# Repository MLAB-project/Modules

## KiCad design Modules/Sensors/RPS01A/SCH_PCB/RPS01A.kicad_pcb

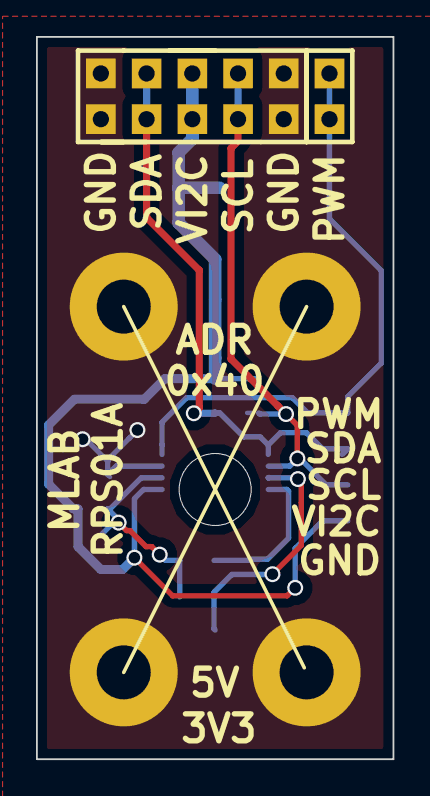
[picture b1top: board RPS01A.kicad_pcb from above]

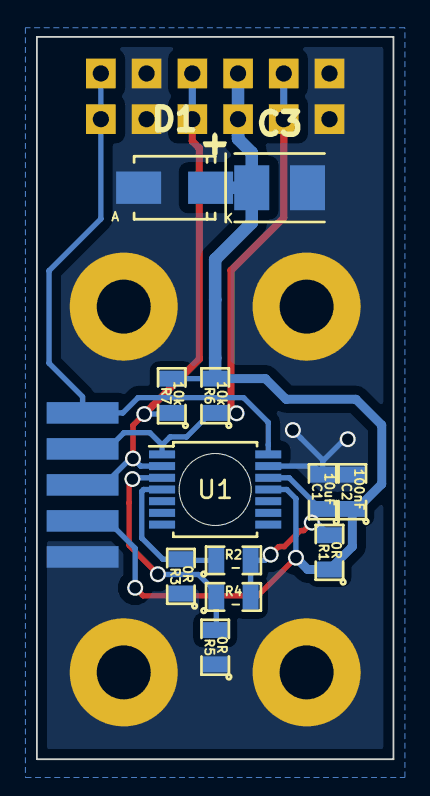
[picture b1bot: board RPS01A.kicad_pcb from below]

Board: 2 copper layers, 19.8 x 40.1 mm, 19 parts (13 on the bottom side), 8 nets.

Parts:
C1: 10uF; SMD-0805
C2: 100nF; SMD-0805
C3: 10uF; TantalC_SizeB_Reflow
D1: M4; SMA_Standard
J1: JUMP_5X2; Pin_Header_Straight_2x05
J2: JUMP_2x1; Pin_Header_Straight_2x01
J3: JUMP_5X2; SMD_JUMP1X5
P1, P2, P3, P4: _; MountingHole_3mm
R1, R3, R5: 0R; SMD-0805
R2, R4: -; SMD-0805
R6, R7: 10k; SMD-0805
U1: AS5048B; TSSOP-14_4.4x5mm_Pitch0.65mm

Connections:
/A1: R2.1, R3.2, U1.4
/A2: R4.1, R5.2, U1.3
/PWM: J2.1, J2.2, J3.5, U1.14
/SCL: J1.2, J1.9, J3.3, R7.1, U1.2
/SDA: J1.4, J1.7, J3.4, R6.1, U1.1
/VDD3V: C1.1, R1.2, R2.2, R4.2, U1.12
GND: C1.2, C2.2, C3.2, D1.1, J1.1, J1.5, J1.6, J1.10, J3.1, P1.1, P2.1, P3.1, P4.1, R3.1, R5.1, U1.13
VDD: C2.1, C3.1, D1.2, J1.3, J1.8, J3.2, R1.1, R6.2, R7.2, U1.11

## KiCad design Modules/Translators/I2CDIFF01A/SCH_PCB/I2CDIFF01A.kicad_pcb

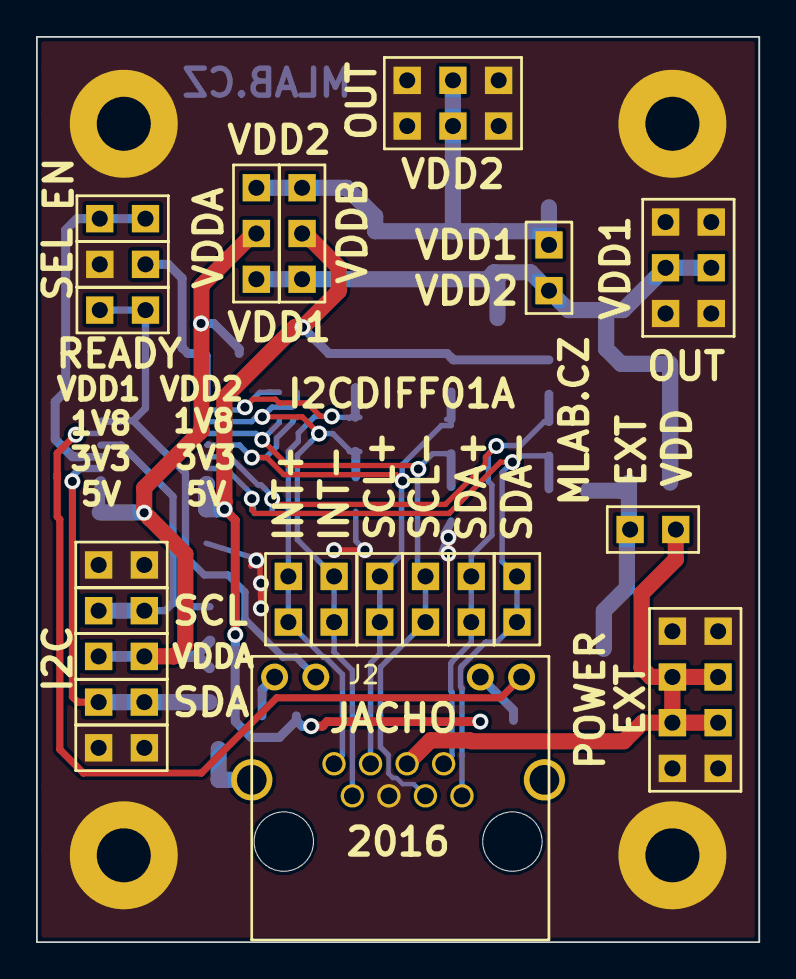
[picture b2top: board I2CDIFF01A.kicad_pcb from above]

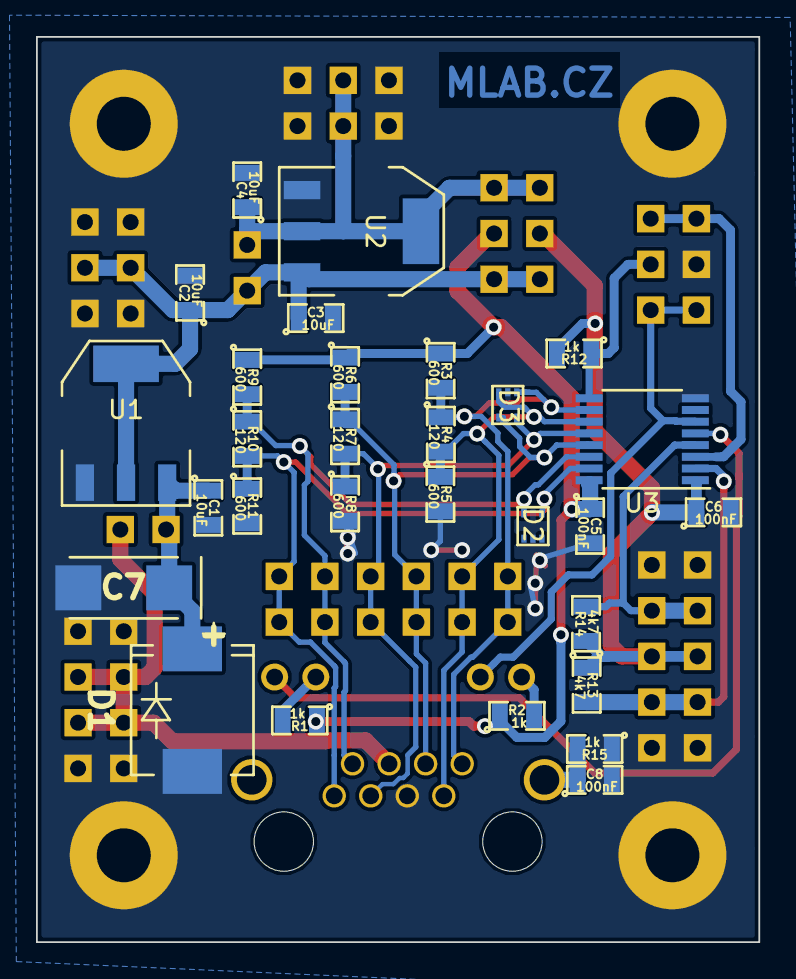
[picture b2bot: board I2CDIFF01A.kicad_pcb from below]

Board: 2 copper layers, 40.1 x 50.3 mm, 55 parts (29 on the bottom side), 22 nets.

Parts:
C1, C2, C3, C4: 10uF; SMD-0805
C5, C6, C8: 100nF; SMD-0805
C7: 47uF; TantalC_SizeC_Reflow
D1: SM15T18A; Diode-SMC_Standard
D2, D3: SP1001-04XTG; SOT-553
J1: JUMP_4X2; Straight_2x04
J2: RJ45_RJHSE-5384; RJHSE-5384(RJ45)
J3, J19, J20, J21, J22, J23: JUMP_2x1; Straight_1x02
J4, J5, J6, J7, J8, J9: JUMP_2x1; Straight_2x01
J10, J13: JUMP_3X2; Straight_2x03
J11, J14, J17: JUMP2_2x1; Straight_2x01
J12, J15: CONN_3; Straight_1x03
J16: EN; Straight_1x02
M1, M2, M3, M4: HOLE; MountingHole_3mm
R1, R2, R12, R15: 1k; SMD-0805
R3, R5, R6, R8, R9, R11: 600; SMD-0805
R4, R7, R10: 120; SMD-0805
R13, R14: 4k7; SMD-0805
U1: LM1117 5V; SOT-223
U2: LM1117 3V3; SOT-223
U3: PCA9616; TSSOP-16_4.4x5mm_Pitch0.65mm

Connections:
/EN: J16.1, J16.2, U3.3
/INT+: D3.1, J2.8, J4.1, J4.2, R3.2, R4.1, U3.10
/INT-: D3.3, J2.7, J5.1, J5.2, R4.2, R5.1, U3.11
/PIDENT: J2.9, U3.5
/READY: J2.11, J3.1, J3.2, U3.6
/SCL+: D3.4, J2.6, J6.1, J6.2, R6.2, R7.1, U3.13
/SCL-: D3.5, J2.3, J7.1, J7.2, R7.2, R8.1, U3.12
/SDA+: D2.5, J2.2, J8.1, J8.2, R9.2, R10.1, U3.14
/SDA-: D2.4, J2.1, J9.1, J9.2, R10.2, R11.1, U3.15
/VDD1: C2.1, C3.1, J10.3, J10.4, J11.2, J12.3, J15.3, U1.2, U1.4, U2.3
/VDD2: C4.1, J11.1, J12.1, J13.3, J13.4, J15.1, U2.2, U2.4
/VddA: C6.1, J15.2, J21.1, J21.2, R12.2, R13.1, R14.1, U3.1
/VddB: C5.1, J12.2, R1.1, R2.1, R3.1, R6.1, R9.1, U3.16
GND: C1.2, C2.2, C3.2, C4.2, C5.2, C6.2, C7.2, C8.2, D1.1, D2.2, D3.2, J1.1, J1.2, J1.7, J1.8, J2.5, J10.1, J10.2, J10.5, J10.6, J13.1, J13.2, J13.5, J13.6, J14.1, J19.1, J19.2, J23.1, J23.2, M1.1, M2.1, M3.1, M4.1, R5.2, R8.2, R11.2, R15.1, U1.1, U2.1, U3.8
unnamed: C8.1, J2.13, R15.2
unnamed: J2.10, R1.2
unnamed: J2.12, R2.2
unnamed: J14.2, R12.1, U3.9
SCL: J22.1, J22.2, R14.2, U3.4
SDA: J20.1, J20.2, R13.2, U3.2
VCC: J1.3, J1.4, J1.5, J1.6, J2.4, J17.2
VDD: C1.1, C7.1, D1.2, J17.1, U1.3

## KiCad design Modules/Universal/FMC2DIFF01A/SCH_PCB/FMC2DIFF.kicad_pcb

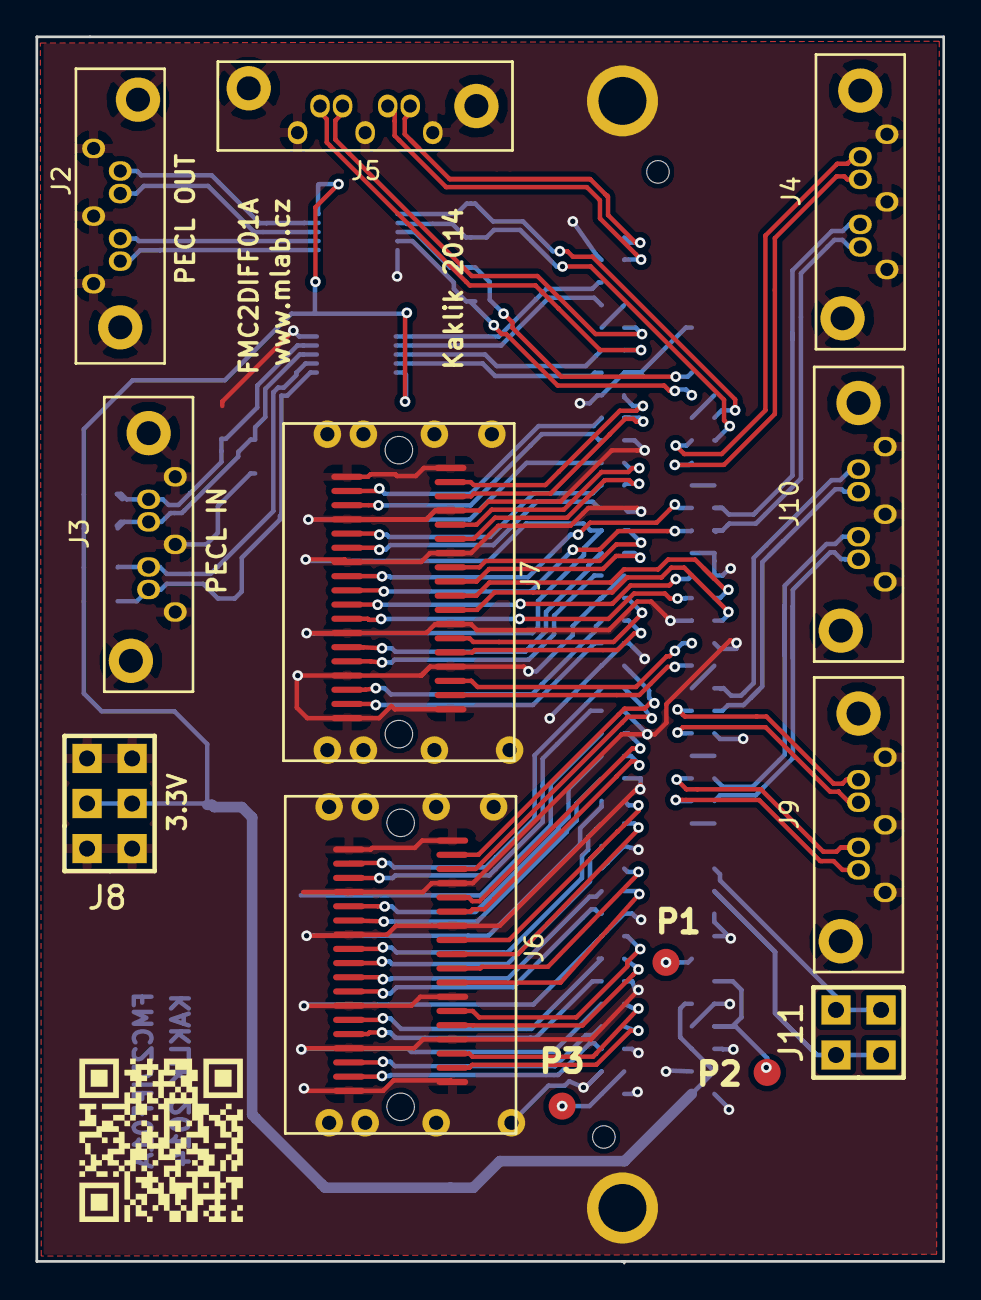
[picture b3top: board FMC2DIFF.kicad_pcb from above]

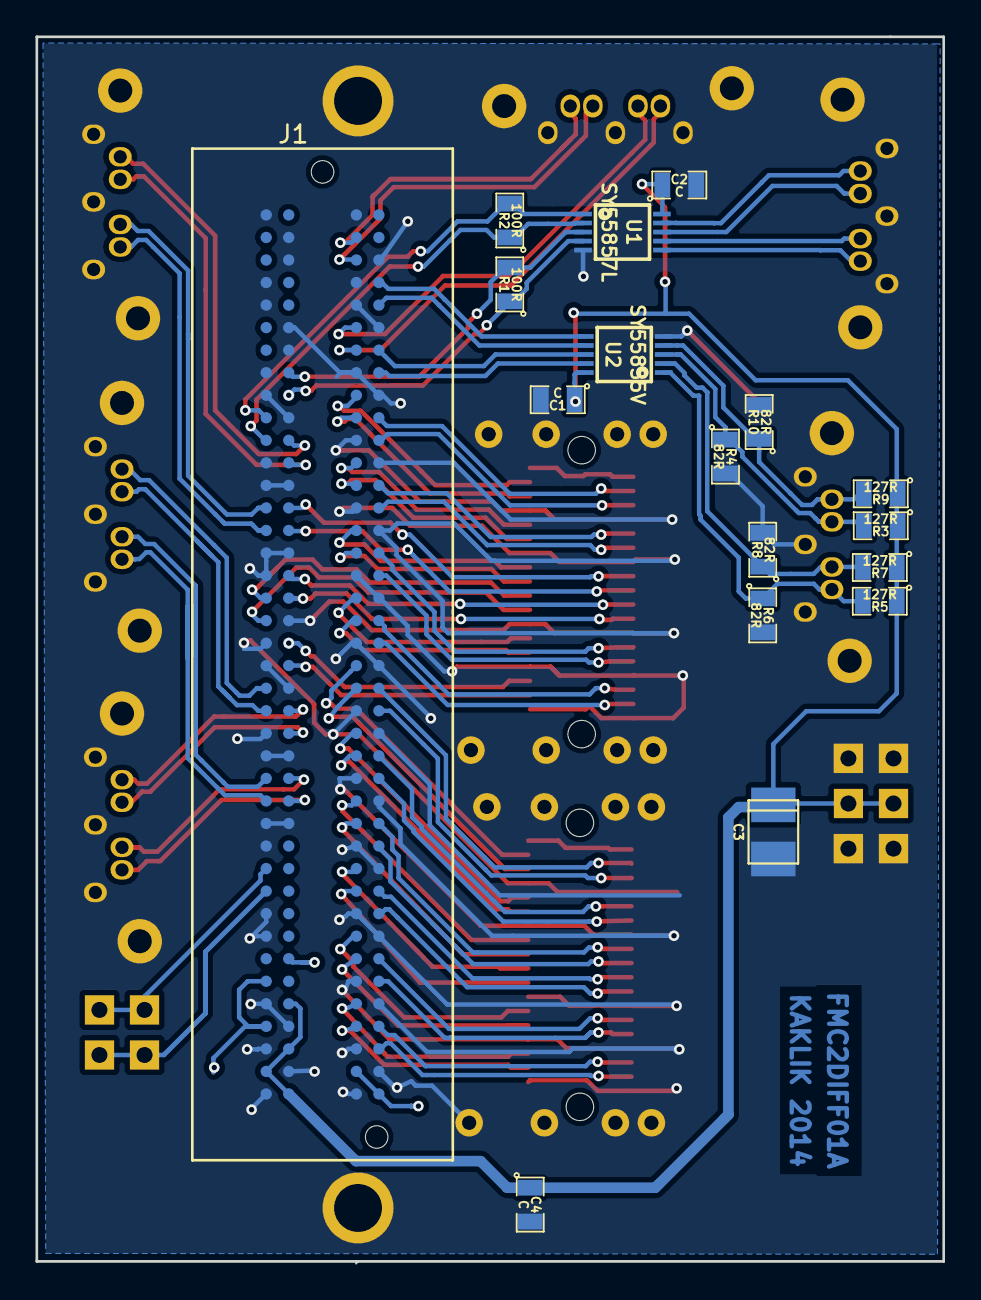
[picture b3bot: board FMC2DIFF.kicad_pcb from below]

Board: 2 copper layers, 51.1 x 69.1 mm, 30 parts (17 on the bottom side), 87 nets.

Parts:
C1, C2, C4: C; SM0805
C3: CP1; c_tant_B
J1: ASP-134604-01_(FMC); FMC_LPC_ASP-134604-01
J2, J3, J4, J5, J9, J10: SATA7-67491-1030; SATA-7_THT_VERT
J6, J7: SAS_mini_1888174
J8: JUMP_3X2_CONN; Pin_Header_Straight_2x03
J11: JUMP_2X2_CONN; Pin_Header_Straight_2x02
P1, P2, P3: CONN_1; Measurement_Point_Round-SMD-Pad_Small
R1, R2: 100R; SM0805
R3, R5, R7, R9: 127R; SM0805
R4, R6, R8, R10: 82R; SM0805
U1: SY55857L; MSOP10-0.5
U2: SY55855V; MSOP10-0.5

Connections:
3V3: C1.1, C2.1, C3.1, C4.1, J1.C39, J1.D36, J1.D38, J1.D40, J8.2, J8.5, R3.1, R5.1, R7.1, R9.1, U1.10, U2.10
+12V: J1.C35, J1.C37, P2.1
CLK0_M2C_N: J1.H05, U2.7
CLK0_M2C_P: J1.H04, U2.6
CLK1_M2C_N: J1.G03, J5.3
CLK1_M2C_P: J1.G02, J5.2
DGND: C1.2, C2.2, C3.2, C4.2, J1.C01, J1.C04, J1.C05, J1.C08, J1.C09, J1.C12, J1.C13, J1.C16, J1.C17, J1.C20, J1.C21, J1.C24, J1.C25, J1.C28, J1.C29, J1.C32, J1.C33, J1.C36, J1.C38, J1.C40, J1.D02, J1.D03, J1.D06, J1.D07, J1.D10, J1.D13, J1.D16, J1.D19, J1.D22, J1.D25, J1.D28, J1.D37, J1.D39, J1.G01, J1.G04, J1.G05, J1.G08, J1.G11, J1.G14, J1.G17, J1.G20, J1.G23, J1.G26, J1.G29, J1.G32, J1.G35, J1.G38, J1.G40, J1.H03, J1.H06, J1.H09, J1.H12, J1.H15, J1.H18, J1.H21, J1.H24, J1.H27, J1.H30, J1.H33, J1.H36, J1.H39, J2.1, J2.4, J2.7, J2.8, J2.9, J3.1, J3.4, J3.7, J3.8, J3.9, J4.1, J4.4, J4.7, J4.8, J4.9, J5.1, J5.4, J5.7, J5.8, J5.9, J6.1, J6.2, J6.3, J6.4, J6.5, J6.6, J6.7, J6.8, J6.A1, J6.A4, J6.A7, J6.A12, J6.A15, J6.A18, J6.B1, J6.B4, J6.B7, J6.B12, J6.B15, J6.B18, J7.1, J7.2, J7.3, J7.4, J7.5, J7.6, J7.7, J7.8, J7.A1, J7.A4, J7.A7, J7.A12, J7.A15, J7.A18, J7.B1, J7.B4, J7.B7, J7.B12, J7.B15, J7.B18, J8.1, J8.3, J8.4, J8.6, J9.1, J9.4, J9.7, J9.8, J9.9, J10.1, J10.4, J10.7, J10.8, J10.9, R4.2, R6.2, R8.2, R10.2, U1.5, U2.5
LA00_N_CC: J1.G07, J5.6
LA00_P_CC: J1.G06, J5.5
LA01_N_CC: J1.D09, R1.1, U1.4
LA01_P_CC: J1.D08, R1.2, U1.3
LA02_N: J1.H08, U2.9
LA02_P: J1.H07, U2.8
LA03_N: J1.G10, J7.B3
LA03_P: J1.G09, J7.B2
LA04_N: J1.H11, J7.A3
LA04_P: J1.H10, J7.A2
LA05_N: J1.D12, J4.3
LA05_P: J1.D11, J4.2
LA06_N: J1.C11, R2.1, U1.2
LA06_P: J1.C10, R2.2, U1.1
LA07_N: J1.H14, J7.A6
LA07_P: J1.H13, J7.A5
LA08_N: J1.G13, J7.B6
LA08_P: J1.G12, J7.B5
LA09_N: J1.D15, J7.A9
LA09_P: J1.D14, J7.A8
LA10_N: J1.C15, J4.6
LA10_P: J1.C14, J4.5
LA11_N: J1.H17, J7.A14
LA11_P: J1.H16, J7.A13
LA12_N: J1.G16, J7.B9
LA12_P: J1.G15, J7.B8
LA13_N: J1.D18, J7.A11
LA13_P: J1.D17, J7.A10
LA14_N: J1.C19, J7.B11
LA14_P: J1.C18, J7.B10
LA15_N: J1.H20, J7.A17
LA15_P: J1.H19, J7.A16
LA16_N: J1.G19, J7.B14
LA16_P: J1.G18, J7.B13
LA17_N_CC: J1.D21, J7.B17
LA17_P_CC: J1.D20, J7.B16
LA18_N_CC: J1.C23, J10.3
LA18_P_CC: J1.C22, J10.2
LA19_N: J1.H23, J6.A3
LA19_P: J1.H22, J6.A2
LA20_N: J1.G22, J6.B3
LA20_P: J1.G21, J6.B2
LA21_N: J1.H26, J6.A6
LA21_P: J1.H25, J6.A5
LA22_N: J1.G25, J6.B6
LA22_P: J1.G24, J6.B5
LA23_N: J1.D24, J9.3
LA23_P: J1.D23, J9.2
LA24_N: J1.H29, J6.A9
LA24_P: J1.H28, J6.A8
LA25_N: J1.G28, J6.B9
LA25_P: J1.G27, J6.B8
LA26_N: J1.D27, J9.6
LA26_P: J1.D26, J9.5
LA27_N: J1.C27, J10.6
LA27_P: J1.C26, J10.5
LA28_N: J1.H32, J6.A11
LA28_P: J1.H31, J6.A10
LA29_N: J1.G31, J6.B11
LA29_P: J1.G30, J6.B10
LA30_N: J1.H35, J6.A14
LA30_P: J1.H34, J6.A13
LA31_N: J1.G34, J6.B14
LA31_P: J1.G33, J6.B13
LA32_N: J1.H38, J6.A17
LA32_P: J1.H37, J6.A16
LA33_N: J1.G37, J6.B17
LA33_P: J1.G36, J6.B16
unnamed: J2.2, U1.6
unnamed: J2.3, U1.7
unnamed: J2.5, U1.8
unnamed: J2.6, U1.9
unnamed: J3.2, R9.2, R10.1, U2.4
unnamed: J3.3, R3.2, R4.1, U2.3
unnamed: J3.5, R7.2, R8.1, U2.2
unnamed: J3.6, R5.2, R6.1, U2.1
SCL: J1.C30, J11.2, J11.3
SDA: J1.C31, J11.1, J11.4
TRST_L: J1.D34, P1.1
VDD: J1.G39, J1.H40, P3.1

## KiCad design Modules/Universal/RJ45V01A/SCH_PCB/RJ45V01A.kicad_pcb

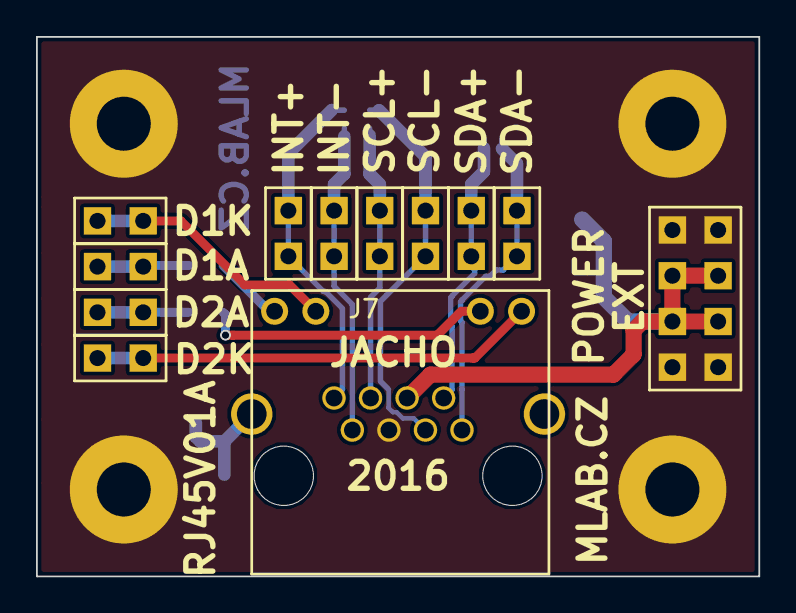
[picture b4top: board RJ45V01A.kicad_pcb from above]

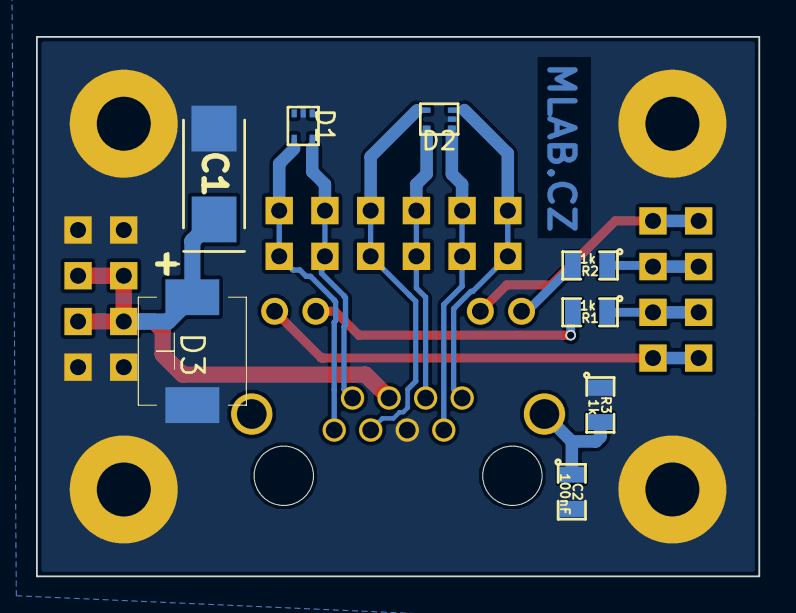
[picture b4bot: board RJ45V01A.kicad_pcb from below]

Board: 2 copper layers, 40.1 x 30.0 mm, 24 parts (8 on the bottom side), 15 nets.

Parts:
C1: 47uF; TantalC_SizeC_Reflow
C2: 100nF; SMD-0805
D1, D2: SP1001-04XTG; SOT-553
D3: SM15T18A; Diode-SMC_Standard
J1: JUMP_4X2; Straight_2x04
J3: JUMP_2x1; Straight_1x02
J4, J5, J6, J8, J9, J10, J11, J12, J13: JUMP_2x1; Straight_2x01
J7: RJ45_RJHSE-5384; RJHSE-5384(RJ45)
M1, M2, M3, M4: HOLE; MountingHole_3mm
R1, R2, R3: 1k; SMD-0805

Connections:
/D1_A: J6.1, J6.2, R2.1
/D1_K: J3.1, J3.2, J7.11
/D2_A: J5.1, J5.2, R1.1
/D2_K: J4.1, J4.2, J7.9
/INT+: D2.3, J7.8, J8.1, J8.2
/INT-: D2.1, J7.7, J9.1, J9.2
/SCL+: D2.5, J7.6, J10.1, J10.2
/SCL-: D2.4, J7.3, J11.1, J11.2
/SDA+: D1.5, J7.2, J12.1, J12.2
/SDA-: D1.4, J7.1, J13.1, J13.2
GND: C1.2, C2.2, D1.2, D2.2, D3.1, J1.1, J1.2, J1.7, J1.8, J7.5, M1.1, M2.1, M3.1, M4.1, R3.1
unnamed: C2.1, J7.13, R3.2
unnamed: J7.10, R1.2
unnamed: J7.12, R2.2
VCC: C1.1, D3.2, J1.3, J1.4, J1.5, J1.6, J7.4

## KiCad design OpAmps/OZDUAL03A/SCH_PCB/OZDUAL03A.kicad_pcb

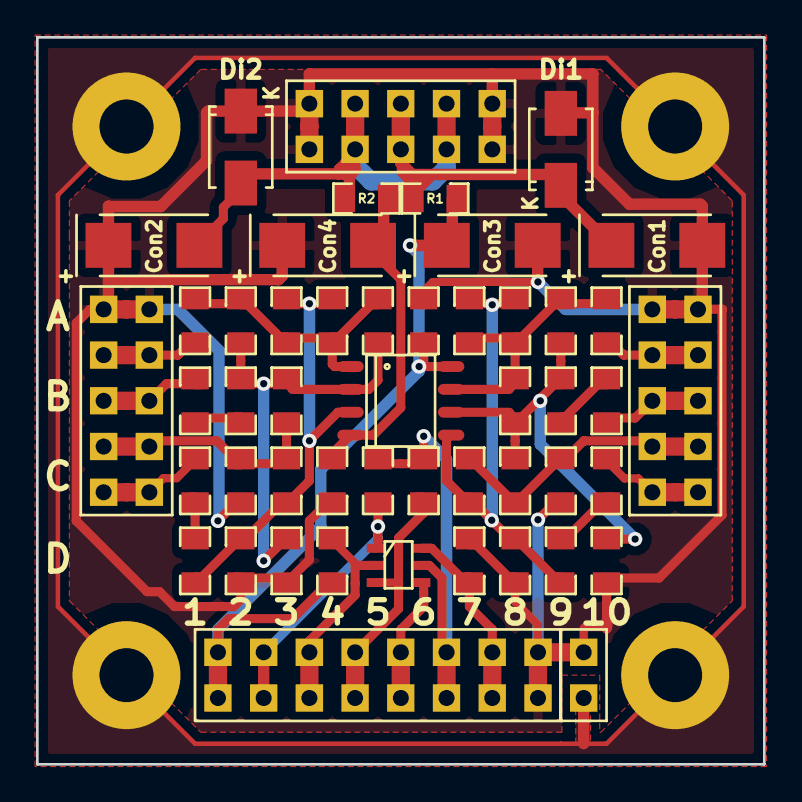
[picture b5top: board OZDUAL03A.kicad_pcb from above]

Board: 2 copper layers, 40.4 x 40.4 mm, 53 parts (0 on the bottom side), 30 nets.

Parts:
A1, A3, A5, A7, A10: C; SMD-0805-hand-soldering
A2, A4, A8, A9: R; SMD-0805-hand-soldering
A6: 100nF; SMD-0805-hand-soldering
B1, B8, B10: C; SMD-0805-hand-soldering
B2, B3, B9: R; SMD-0805-hand-soldering
C1, C2, C5, C6, C9, C10: C; SMD-0805-hand-soldering
C3, C7, C8: R; SMD-0805-hand-soldering
C4: 100nF; SMD-0805-hand-soldering
Con1, Con2, Con3, Con4: 47u; TantalC_SizeC_Reflow
D1, D2, D3, D4, D7, D8, D9, D10: R; SMD-0805-hand-soldering
Di1, Di2: M4; Diode-SMA_Standard
J1: JUMP2_2x1; Straight_2x01
J2: POWER; Straight_2x05
J3: OPAMPA; Straight_2x05
J4: OPAMPB; Straight_2x05
J5: SOT23-6; Straight_2x08
M1, M2, M3, M4: HOLE; MountingHole_3mm
R1, R2: R; SMD-0805-hand-soldering
U1: OZ; SO-8
U2: sot23-6; SOT-23-6

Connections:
/1: C5.1, J5.13, J5.14, U2.1
/2: D4.2, J5.11, J5.12, U2.2
/3: C6.2, J5.9, J5.10, U2.3
/4: J5.7, J5.8, U2.4
/5: C5.2, C6.1, J5.5, J5.6, U2.5
/6: D7.1, J5.3, J5.4, U2.6
/INA+: C1.1, J3.1, J3.2
/INA-: B1.1, J3.5, J3.6
/INB+: C10.1, J4.1, J4.2
/INB-: B10.1, J4.5, J4.6
/OUTA: A1.1, J3.7, J3.8
/OUTB: A10.1, J4.7, J4.8
/VIN+: Con1.1, Di1.1, J2.5, J2.6, R1.2
/VIN-: Con2.2, Di2.2, J2.3, J2.4, J2.7, J2.8, R2.2
/VREFA: B3.2, C2.1, C3.2, J3.3, J3.4
/VREFB: C7.2, C8.2, C9.1, J4.3, J4.4
GND: J1.2, M1.1, M2.1, M3.1, M4.1
GNDA: A6.2, C2.2, C4.1, C9.2, Con1.2, Con2.1, Con3.2, Con4.1, D2.2, D3.2, D7.2, D8.1, D10.1, Di1.2, Di2.1, J1.1, J2.1, J2.2, J2.9, J2.10, J3.9, J3.10, J4.9, J4.10, J5.1, J5.2
unnamed: A1.2, A2.1, A3.2, A4.1, A5.2, U1.1
unnamed: A2.2, A5.1, B2.1, B3.1, D3.1, U1.2
unnamed: A3.1, A4.2, C3.1, D1.1, D2.1, U1.3
unnamed: A7.1, A8.2, C7.1, D8.2, D9.1, U1.5
unnamed: A9.2, B8.1, B9.1, C8.1, D10.2, U1.6
unnamed: A7.2, A8.1, A9.1, A10.2, B8.2, U1.7
unnamed: B1.2, B2.2
unnamed: B9.2, B10.2
unnamed: C1.2, D1.2
unnamed: C10.2, D9.2
VCC: A6.1, Con3.1, D4.1, J5.15, J5.16, R1.1, U1.8
VSS: C4.2, Con4.2, R2.1, U1.4

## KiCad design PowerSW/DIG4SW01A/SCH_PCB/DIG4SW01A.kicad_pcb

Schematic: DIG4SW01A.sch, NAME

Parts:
C1: 47uF/63V; C_Radial_D6.3_L11.2_P2.5
C3: 47uF/16V; TantalC_SizeC_Reflow
C4: 100pF; SMD-0805
D1: STPS340U; Diode-SMB_Standard
D2, D3, D4, D5: SMBJ15A-E3/52; SMB_Standard
J1, J2: CONN1_1; WAGO256
J3: CONN1_2; Straight_1x02
J4, J5, J6, J7, J8, J9, J10, J11, J12, J13: JUMP_2x1; Straight_2x01
J14, J15, J16, J17: JUMP_4X2; Straight_2x04
M1, M2, M3, M4: HOLE; MountingHole_3mm
R1, R2, R4, R5, R6, R7, R8, R9, R10, R11: 4k7; SMD-0805
R3: 1k2; SMD-0805
R12: 820R; SMD-0805
R13: -; SMD-0805
R14, R15, R16, R17: 20k; SMD-0805
U1: TPS4H160-Q1-B; HTSSOP28

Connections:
/#FAULT: J4.1, J4.2, R2.2
/CS: C4.1, J5.1, J5.2, R1.2
/DIAG_EN: J12.1, J12.2, R10.2
/IN1: J6.1, J6.2, R4.2
/IN2: J7.1, J7.2, R5.2
/IN3: J8.1, J8.2, R6.2
/IN4: J9.1, J9.2, R7.2
/OUT1: D2.1 (K), J14.3 (4), J14.4, J14.5, J14.6 (5), R14.1, U1.27 (OUT1), U1.28 (OUT1)
/OUT2: D3.1 (K), J15.3 (4), J15.4, J15.5, J15.6 (5), R15.1, U1.25 (OUT2), U1.26 (OUT2)
/OUT3: D4.1 (K), J16.3 (4), J16.4, J16.5, J16.6 (5), R16.1, U1.17 (OUT3), U1.18 (OUT3)
/OUT4: D5.1 (K), J17.3 (4), J17.4, J17.5, J17.6 (5), R17.1, U1.15 (OUT4), U1.16 (OUT4)
/SEH: J10.1, J10.2, R8.2
/SEL: J11.1, J11.2, R9.2
/THER: J13.1, J13.2, R13.2, U1.13 (THER)
GND: C1.2, C3.2, C4.2, D1.2 (A), D2.2 (A), D3.2 (A), D4.2 (A), D5.2 (A), J2.1, J3.2, J14.1 (2), J14.2, J14.7 (8), J14.8, J15.1 (2), J15.2, J15.7 (8), J15.8, J16.1 (2), J16.2, J16.7 (8), J16.8, J17.1 (2), J17.2, J17.7 (8), J17.8, M1.1, M2.1, M3.1, M4.1, R3.1, R12.1, R13.1, U1.1 (GND), U1.12 (GND), U1.29
unnamed: R1.1, R3.2, U1.10 (CS)
unnamed: R4.1, U1.3 (IN1)
unnamed: R5.1, U1.4 (IN2)
unnamed: R6.1, U1.5 (IN3)
unnamed: R7.1, U1.6 (IN4)
unnamed: R8.1, U1.7 (SEH)
unnamed: R9.1, U1.8 (SEL)
unnamed: R10.1, U1.14 (DIAG_EN)
unnamed: R2.1, R11.1, U1.9 (FAULT)
unnamed: R12.2, U1.11 (CL)
VCC: C1.1, C3.1, D1.1 (K), J1.1, J3.1, R11.2, R14.2, R15.2, R16.2, R17.2, U1.20 (VS), U1.21 (VS), U1.22 (VS), U1.23 (VS)

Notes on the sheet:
MOUNTING HOLES

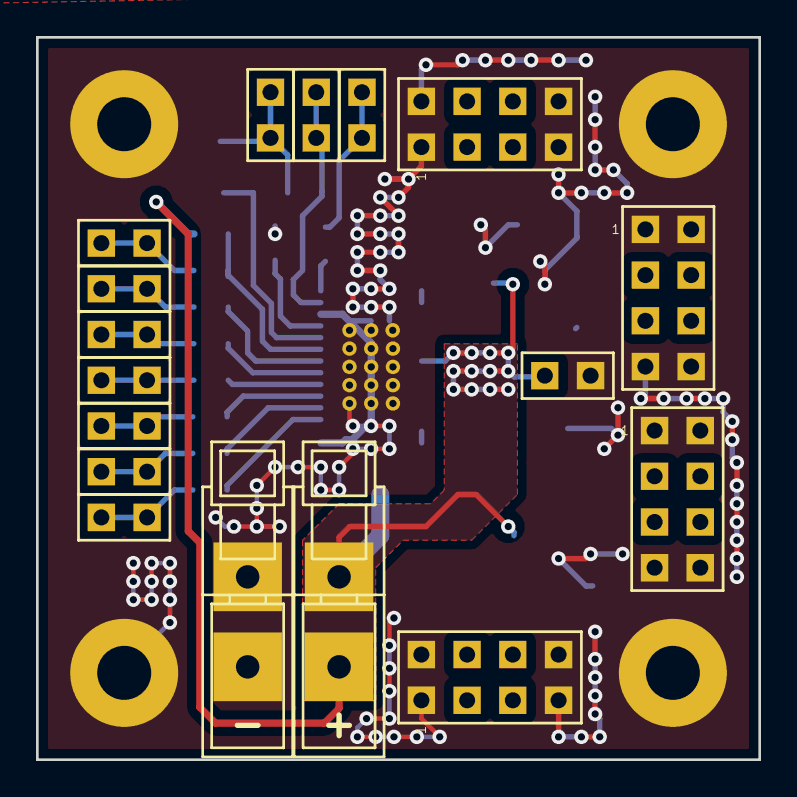
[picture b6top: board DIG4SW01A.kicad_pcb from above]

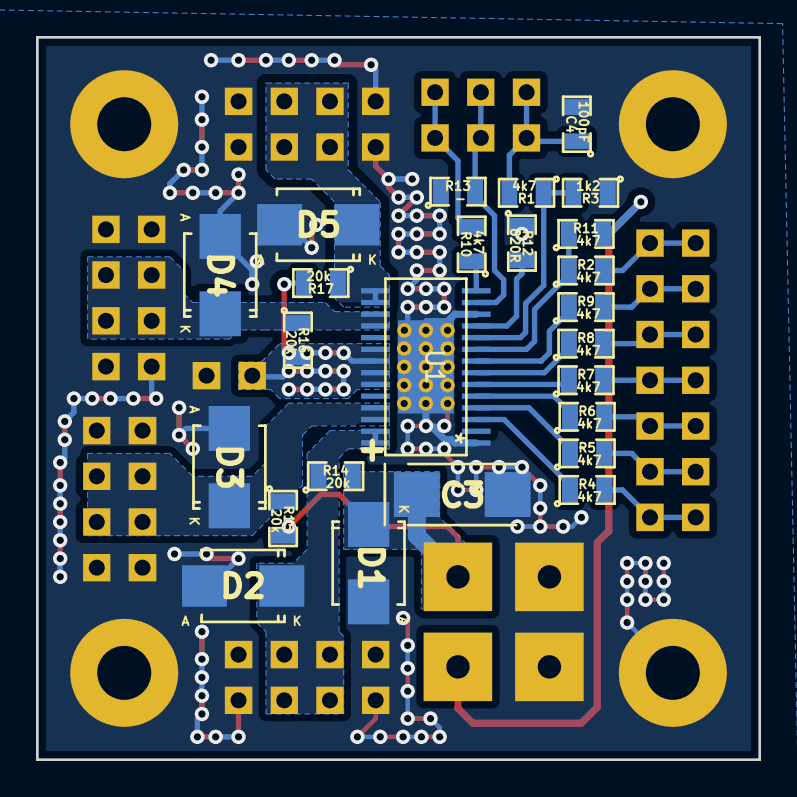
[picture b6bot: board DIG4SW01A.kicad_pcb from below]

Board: 2 copper layers, 40.1 x 40.1 mm, 46 parts (25 on the bottom side), 26 nets.
